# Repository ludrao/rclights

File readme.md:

# RC Lights control system

### Basic feature list:
* Two On/Off (PWM) outputs (fronts lights and rear lights)
* Two inputs (radio signal) (engine, and lights switch)
* One setup button.

### More descriptive feature:
The system captures the engine level, and switch on the rear lights when breaking. The lights switch (on a 3rd chanel) allows to switch on/off the front lights and the rear lights at 30% power (night mode).

The current software works for a RC Lights control system.

However, the hardware platform could be retrofited for any uses cases requirering 2 PWM outputs and 2 IN/OUT radio signal channels.
It is based on a PIC 12F1840, programmable directly in C (I used MPLABX for this project...)

### Some hardware details:
* MCU is a PIC12F1840, low power
* MCU powered at 3.3V linear regulator (ideally LDO to support low BEC)
* The two output have BS170 (N-Mosfet) supporting up to 500mA continuous load

The PCB is single face, with through hole components. It could be easily be converted int a surface mount PCB, thus reducing further the size of the PCB (basically the size of the button+connector). Please let me know if you are interested...

Here is an export of the schematic (the sources files are in Eagle format in the hw directory).

The full system, assembled and under test on my TB-04 Chassis...

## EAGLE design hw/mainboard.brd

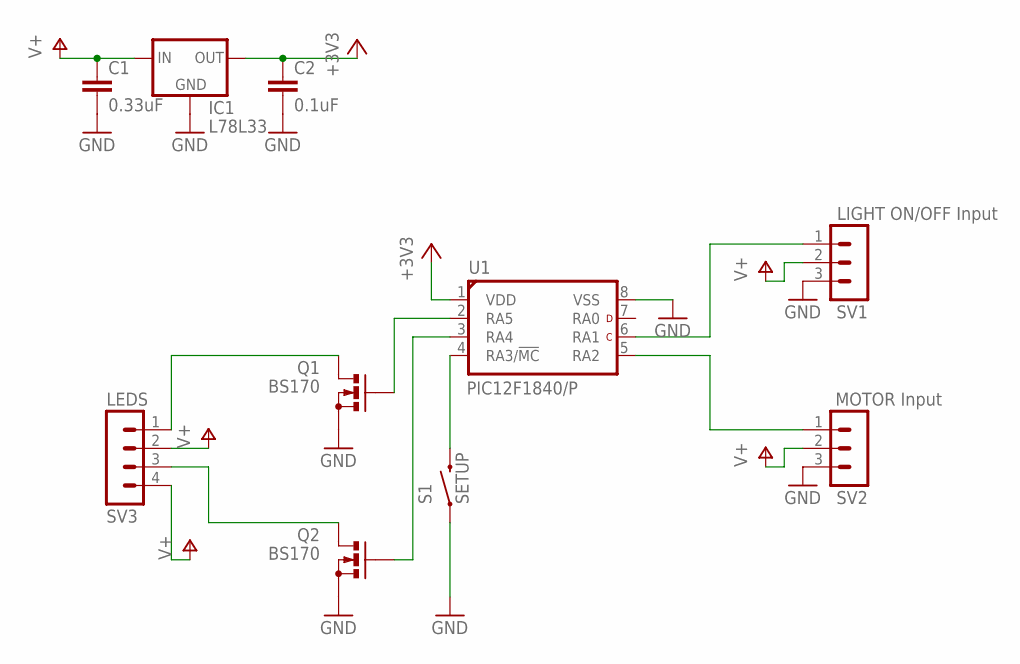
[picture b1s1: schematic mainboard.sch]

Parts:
C1: 0.33uF; C025-025X050
C2: 0.1uF; C025-025X050
IC1: L78L33; 78LXX
Q1, Q2: BS170; SOT54E
S1: SETUP; TACTILE-PTH
SV1: LIGHT ON/OFF Input; MA03-1
SV2: MOTOR Input; MA03-1
SV3: LEDS; MA04-1
U1: PIC12F1840/P; DIL8-P

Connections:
+3V3: C2.1, IC1.OUT, U1.1 (VDD)
GND: C1.2, C2.2, IC1.GND, Q1.S, Q2.S, S1.1, SV1.3, SV2.3, U1.8 (VSS)
unnamed: Q1.D, SV3.1
unnamed: Q1.G, U1.2 (RA5)
unnamed: Q2.G, U1.3 (RA4)
unnamed: Q2.D, SV3.3
unnamed: SV2.1, U1.5 (RA2)
unnamed: SV1.1, U1.6 (RA1)
unnamed: S1.3 (2), U1.4 (RA3/!MC!)
V+: C1.1, IC1.IN, SV1.2, SV2.2, SV3.2, SV3.4

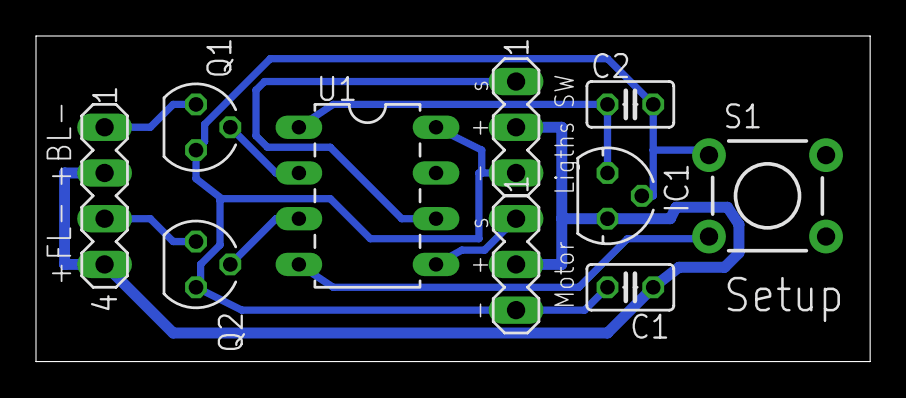
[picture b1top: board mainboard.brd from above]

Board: 2 copper layers, 46.3 x 18.1 mm, 10 parts (0 on the bottom side), 10 nets.

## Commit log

2015-09-27 First load of the project
2015-09-27 Fixed image name in readme.md
2015-09-27 Add readable schematic export in readme.md
2015-10-14 Update readme.md
    Fixed minor typo

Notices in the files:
parts and their libraries:
SparkFun-Electromechanical: Licensing: Creative Commons ShareAlike 4.0 International - https://creativecommons.org/licenses/by-sa/4.0
